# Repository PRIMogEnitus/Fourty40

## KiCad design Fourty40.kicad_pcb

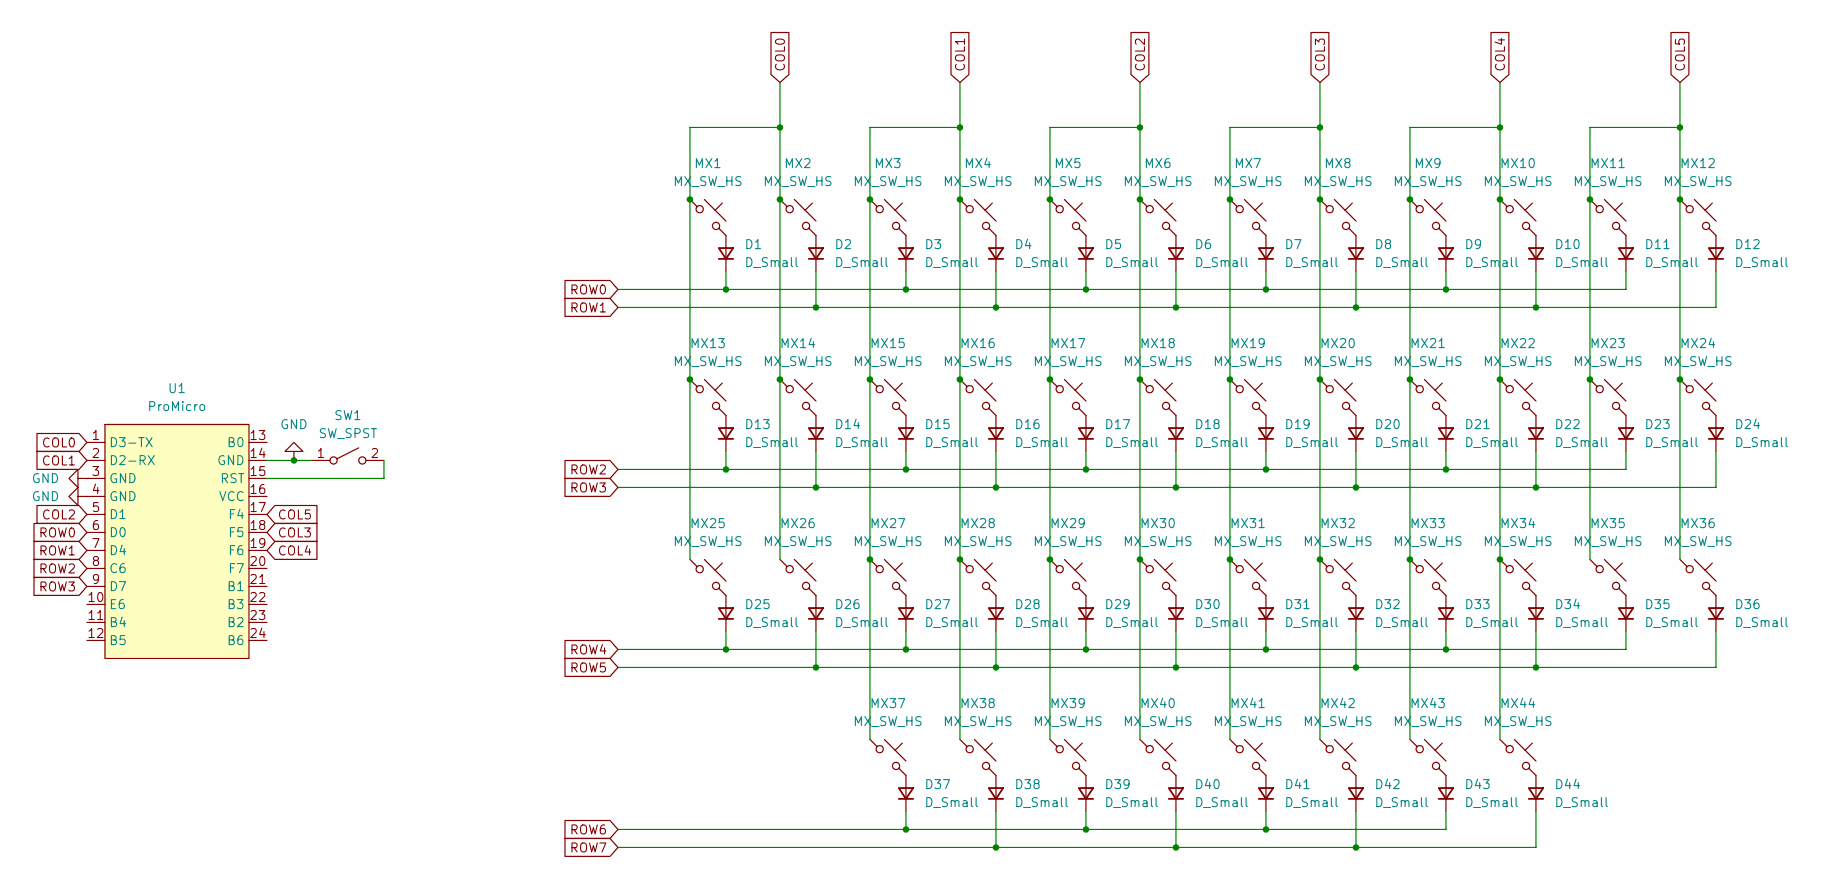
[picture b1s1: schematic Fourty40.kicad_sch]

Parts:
D1, D2, D3, D4, D5, D6, D7, D8, D9, D10, D11, D12, D13, D14, D15, D16, D17, D18, D19, D20, D21, D22, D23, D24, D25, D26, D27, D28, D29, D30, D31, D32, D33, D34, D35, D36, D37, D38, D39, D40, D41, D42, D43, D44: D_Small; D_SOD-123
MX1, MX2, MX3, MX4, MX5, MX6, MX7, MX8, MX9, MX10, MX11, MX12, MX13, MX14, MX15, MX16, MX17, MX18, MX19, MX20, MX21, MX22, MX23, MX24, MX25, MX26, MX27, MX28, MX29, MX30, MX31, MX32, MX33, MX34, MX35, MX36, MX37, MX38, MX39, MX40, MX41, MX42, MX43, MX44: MX_SW_HS; SW_MX_HS_1u
SW1: SW_SPST; TACTILE_SWITCH_SMD_6.0X3.5MM
U1: ProMicro; ProMicro_USBup

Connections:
COL0: MX1.1, MX2.1, MX13.1, MX14.1, MX25.1, MX26.1, U1.1 (D3-TX)
COL1: MX3.1, MX4.1, MX15.1, MX16.1, MX27.1, MX28.1, MX37.1, MX38.1, U1.2 (D2-RX)
COL2: MX5.1, MX6.1, MX17.1, MX18.1, MX29.1, MX30.1, MX39.1, MX40.1, U1.5 (D1)
COL3: MX7.1, MX8.1, MX19.1, MX20.1, MX31.1, MX32.1, MX41.1, MX42.1, U1.18 (F5)
COL4: MX9.1, MX10.1, MX21.1, MX22.1, MX33.1, MX34.1, MX43.1, MX44.1, U1.19 (F6)
COL5: MX11.1, MX12.1, MX23.1, MX24.1, MX35.1, MX36.1, U1.17 (F4)
GND: SW1.1 (A), U1.3 (GND), U1.4 (GND), U1.14 (GND)
unnamed: D1.2 (A), MX1.2
unnamed: D2.2 (A), MX2.2
unnamed: D3.2 (A), MX3.2
unnamed: D4.2 (A), MX4.2
unnamed: D5.2 (A), MX5.2
unnamed: D6.2 (A), MX6.2
unnamed: D7.2 (A), MX7.2
unnamed: D8.2 (A), MX8.2
unnamed: D9.2 (A), MX9.2
unnamed: D10.2 (A), MX10.2
unnamed: D11.2 (A), MX11.2
unnamed: D12.2 (A), MX12.2
unnamed: D13.2 (A), MX13.2
unnamed: D14.2 (A), MX14.2
unnamed: D15.2 (A), MX15.2
unnamed: D16.2 (A), MX16.2
unnamed: D17.2 (A), MX17.2
unnamed: D18.2 (A), MX18.2
unnamed: D19.2 (A), MX19.2
unnamed: D20.2 (A), MX20.2
unnamed: D21.2 (A), MX21.2
unnamed: D22.2 (A), MX22.2
unnamed: D23.2 (A), MX23.2
unnamed: D24.2 (A), MX24.2
unnamed: D25.2 (A), MX25.2
unnamed: D26.2 (A), MX26.2
unnamed: D27.2 (A), MX27.2
unnamed: D28.2 (A), MX28.2
unnamed: D29.2 (A), MX29.2
unnamed: D30.2 (A), MX30.2
unnamed: D31.2 (A), MX31.2
unnamed: D32.2 (A), MX32.2
unnamed: D33.2 (A), MX33.2
unnamed: D34.2 (A), MX34.2
unnamed: D35.2 (A), MX35.2
unnamed: D36.2 (A), MX36.2
unnamed: D37.2 (A), MX37.2
unnamed: D38.2 (A), MX38.2
unnamed: D39.2 (A), MX39.2
unnamed: D40.2 (A), MX40.2
unnamed: D41.2 (A), MX41.2
unnamed: D42.2 (A), MX42.2
unnamed: D43.2 (A), MX43.2
unnamed: D44.2 (A), MX44.2
unnamed: SW1.2 (B), U1.15 (RST)
ROW0: D1.1 (K), D3.1 (K), D5.1 (K), D7.1 (K), D9.1 (K), D11.1 (K), U1.6 (D0)
ROW1: D2.1 (K), D4.1 (K), D6.1 (K), D8.1 (K), D10.1 (K), D12.1 (K), U1.7 (D4)
ROW2: D13.1 (K), D15.1 (K), D17.1 (K), D19.1 (K), D21.1 (K), D23.1 (K), U1.8 (C6)
ROW3: D14.1 (K), D16.1 (K), D18.1 (K), D20.1 (K), D22.1 (K), D24.1 (K), U1.9 (D7)
ROW4: D25.1 (K), D27.1 (K), D29.1 (K), D31.1 (K), D33.1 (K), D35.1 (K)
ROW5: D26.1 (K), D28.1 (K), D30.1 (K), D32.1 (K), D34.1 (K), D36.1 (K)
ROW6: D37.1 (K), D39.1 (K), D41.1 (K), D43.1 (K)
ROW7: D38.1 (K), D40.1 (K), D42.1 (K), D44.1 (K)

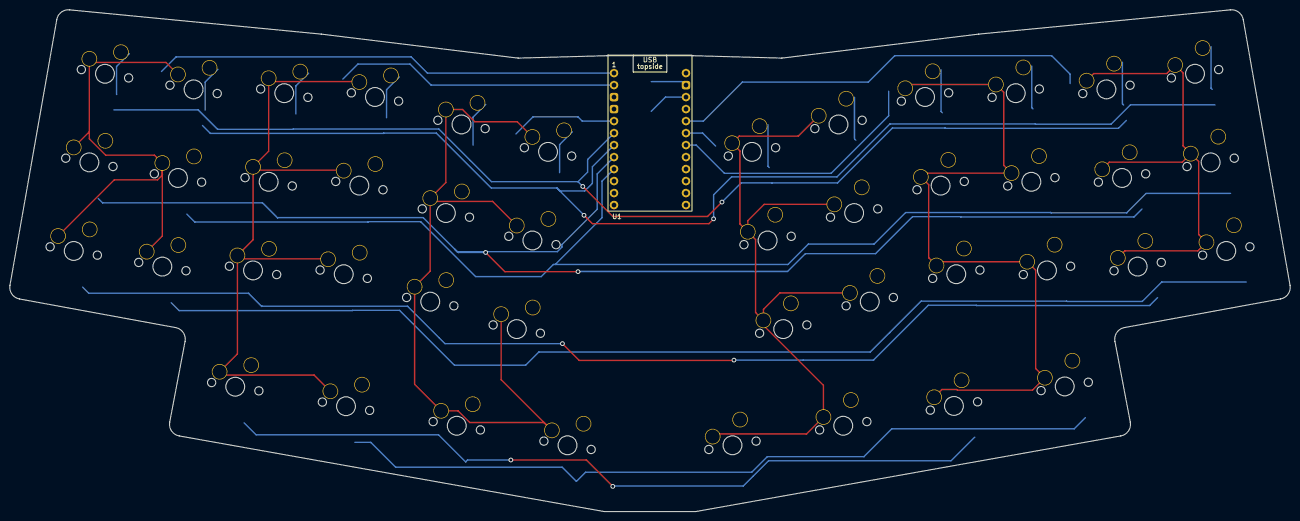
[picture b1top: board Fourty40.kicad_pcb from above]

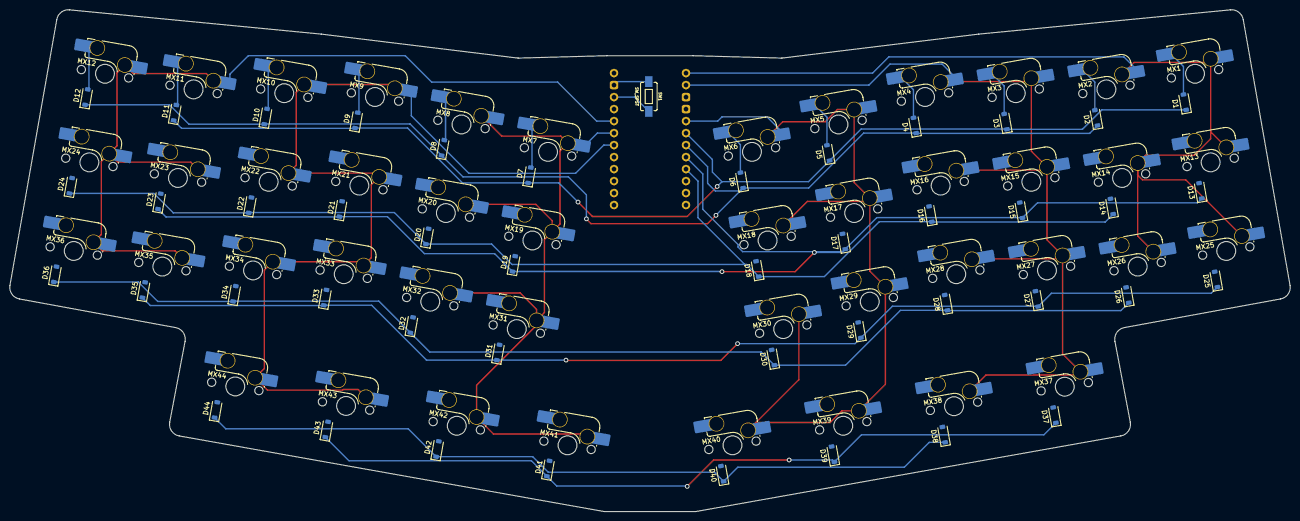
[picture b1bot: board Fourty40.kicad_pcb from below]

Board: 2 copper layers, 271.1 x 106.2 mm, 90 parts (89 on the bottom side), 60 nets.

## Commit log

2024-08-31 Schematics update
2024-08-31 PCB update
